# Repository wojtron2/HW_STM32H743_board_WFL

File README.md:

# HW_STM32H743_board_WFL
An STM32H743 KiCad project board

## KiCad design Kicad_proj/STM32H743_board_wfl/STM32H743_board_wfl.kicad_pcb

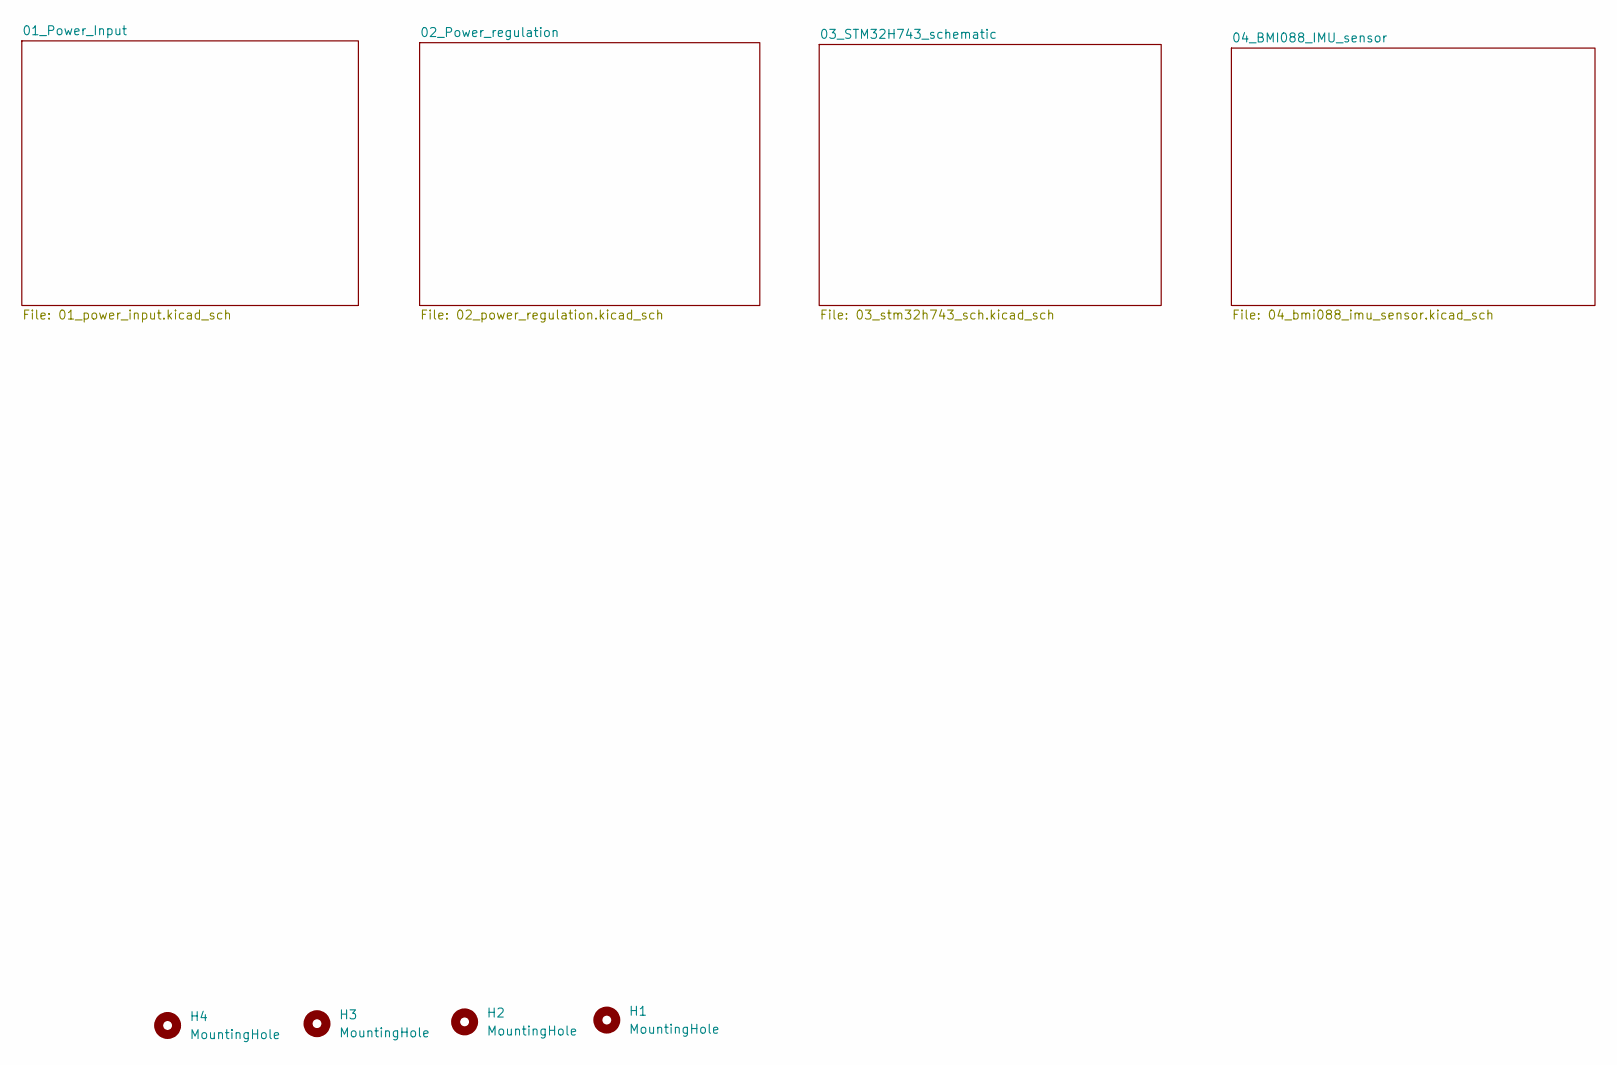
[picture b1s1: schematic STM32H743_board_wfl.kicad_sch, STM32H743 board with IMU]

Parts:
H1, H2, H3, H4: MountingHole; MountingHole_4mm

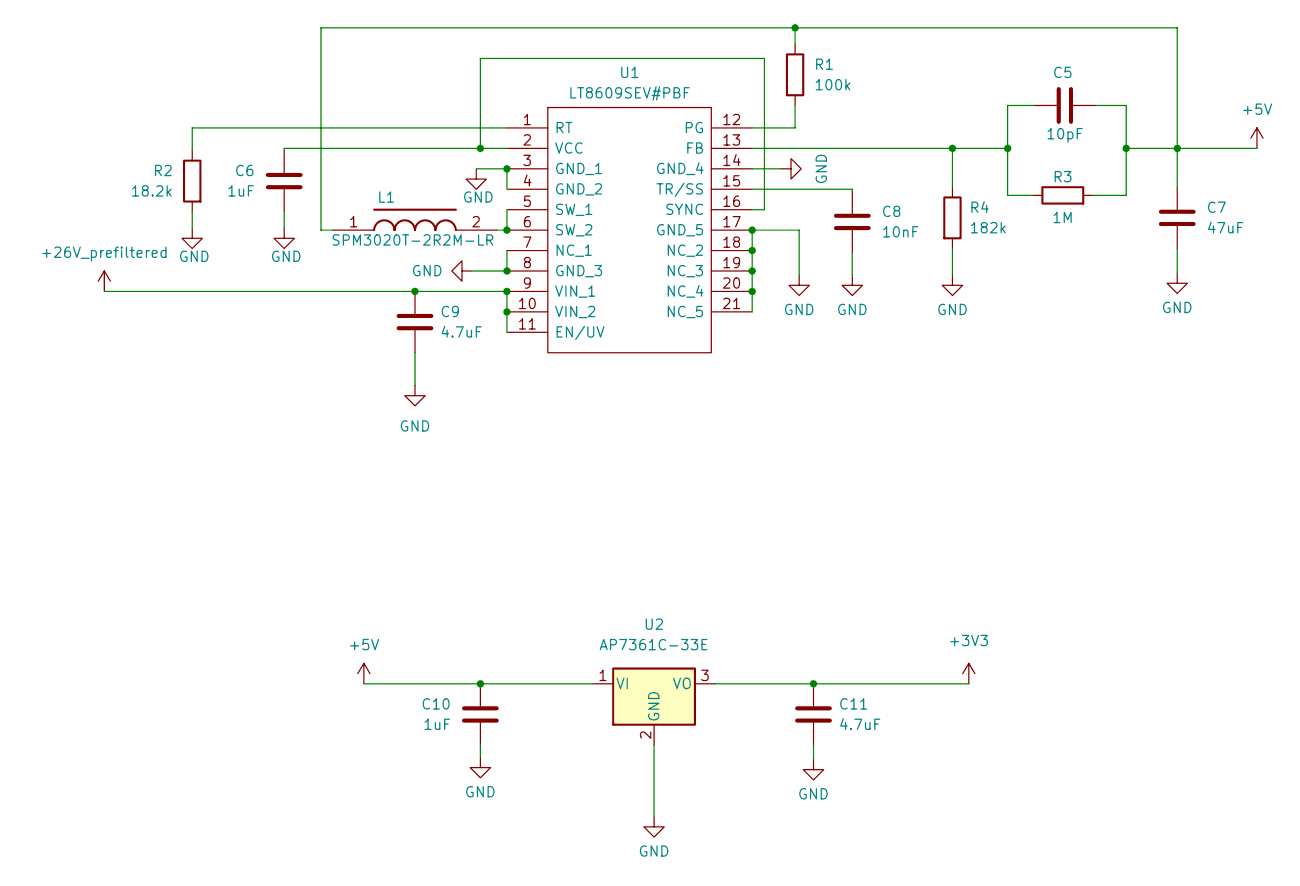
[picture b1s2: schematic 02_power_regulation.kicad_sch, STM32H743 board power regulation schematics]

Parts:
C5: 10pF; C_01005_0402Metric
C6, C10: 1uF; C_0603_1608Metric
C7: 47uF; C_1206_3216Metric
C8: 10nF; C_01005_0402Metric
C9, C11: 4.7uF; C_0603_1608Metric
L1: SPM3020T-2R2M-LR; SPM3010-3020; Mouser Part Number 810-SPM3020T2R2MLR
R1: 100k; R_01005_0402Metric
R2: 18.2k; R_01005_0402Metric
R3: 1M; R_01005_0402Metric
R4: 182k; R_01005_0402Metric
U1: LT8609SEV#PBF; LT8609SEVPBF; Manufacturer_Part_Number LT8609SEV#PBF; Mouser Part Number 584-LT8609SEVPBF
U2: AP7361C-33E; SOT-223-3_TabPin2

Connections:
+5V: C5.2, C7.1, C10.1, L1.1, R1.1, R3.2, U2.1 (VI); also elsewhere on the board
+26V_prefiltered: C9.1, U1.9 (VIN_1), U1.10 (VIN_2), U1.11 (EN/UV); also elsewhere on the board
GND: C6.2, C7.2, C8.2, C9.2, C10.2, C11.2, R2.2, R4.2, U1.3 (GND_1), U1.4 (GND_2), U1.7 (NC_1), U1.8 (GND_3), U1.14 (GND_4), U1.17 (GND_5), U1.18 (NC_2), U1.19 (NC_3), U1.20 (NC_4), U1.21 (NC_5), U2.2 (GND); also elsewhere on the board
unnamed: C5.1, R3.1, R4.1, U1.13 (FB)
unnamed: R1.2, U1.12 (PG)
unnamed: R2.1, U1.1 (RT)
unnamed: L1.2, U1.5 (SW_1), U1.6 (SW_2)
unnamed: C6.1, U1.2 (VCC), U1.16 (SYNC)
unnamed: C8.1, U1.15 (TR/SS)

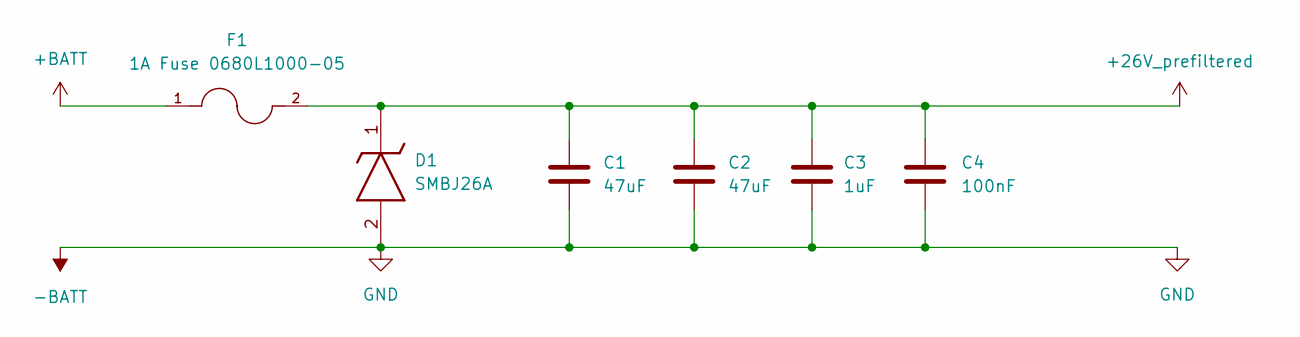
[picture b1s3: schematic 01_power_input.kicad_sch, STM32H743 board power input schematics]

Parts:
C1, C2: 47uF; C_1206_3216Metric
C3: 1uF; C_0603_1608Metric
C4: 100nF; C_01005_0402Metric
D1: SMBJ26A; D_SMB; Manufacturer_Part_Number SMBJ5.0A-E3/5B
F1: 1A Fuse 0680L1000-05; FUSC6125X279N; PARTREV 0679H Apr2019

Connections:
+26V_prefiltered: C1.1, C2.1, C3.1, C4.1, D1.1 (K), F1.2; also elsewhere on the board
+BATT: F1.1; also elsewhere on the board
GND: C1.2, C2.2, C3.2, C4.2, D1.2 (A); also elsewhere on the board

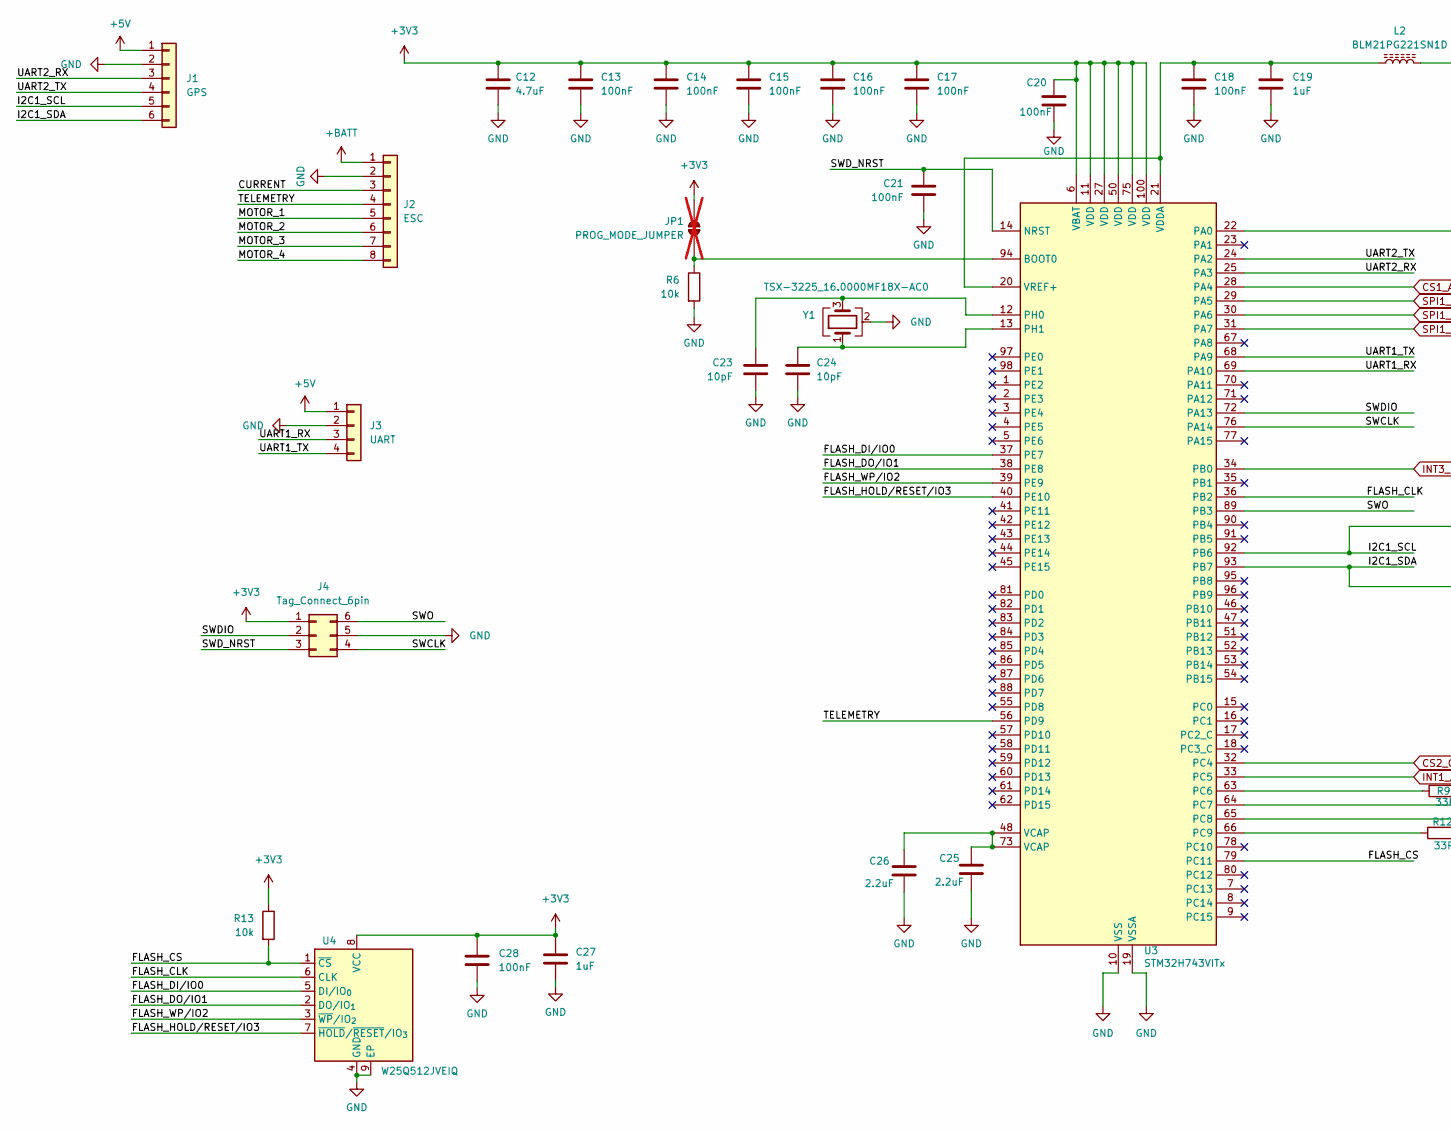
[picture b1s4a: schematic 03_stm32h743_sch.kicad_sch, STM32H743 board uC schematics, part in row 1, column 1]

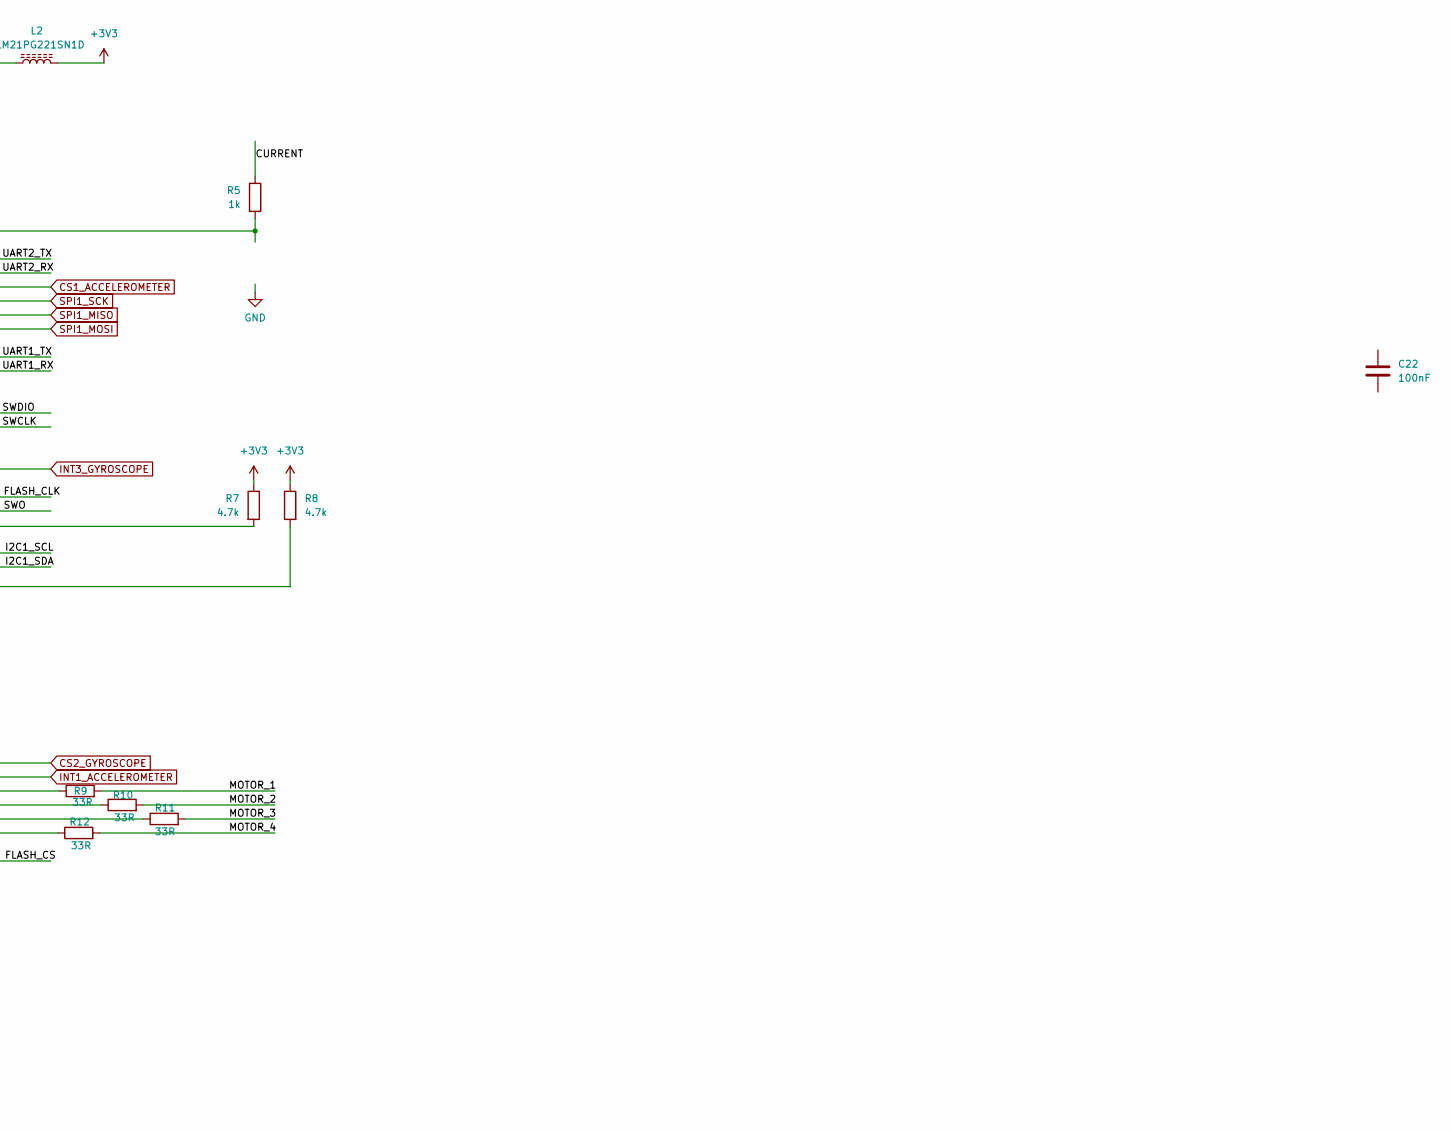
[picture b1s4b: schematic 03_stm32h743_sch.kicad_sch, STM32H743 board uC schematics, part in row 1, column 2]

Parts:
C12: 4.7uF; C_0603_1608Metric
C13, C14, C15, C16, C17, C18, C20, C21, C22, C28: 100nF; C_0402_1005Metric
C19, C27: 1uF; C_0603_1608Metric
C23, C24: 10pF; C_0402_1005Metric
C25, C26: 2.2uF; C_0603_1608Metric
J1: GPS; JST_GH_SM06B-GHS-TB_1x06-1MP_P1.25mm_Horizontal
J2: ESC; JST_GH_SM08B-GHS-TB_1x08-1MP_P1.25mm_Horizontal
J3: UART; JST_GH_SM04B-GHS-TB_1x04-1MP_P1.25mm_Horizontal
J4: Tag_Connect_6pin; Tag-Connect_TC2030-IDC-NL_2x03_P1.27mm_Vertical
JP1: PROG_MODE_JUMPER; R_01005_0402Metric; not fitted
L2: BLM21PG221SN1D; L_0805_2012Metric
R5: 1k; R_01005_0402Metric
R6, R13: 10k; R_01005_0402Metric
R7, R8: 4.7k; R_01005_0402Metric
R9, R10, R11, R12: 33R; R_01005_0402Metric
U3: STM32H743VITx; LQFP-100_14x14mm_P0.5mm
U4: W25Q512JVEIQ; WSON-8-1EP_6x5mm_P1.27mm_EP3.4x4.3mm
Y1: TSX-3225_16.0000MF18X-AC0; Crystal_SMD_3225-4Pin_3.2x2.5mm

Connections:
+5V: J1.1, J3.1; also elsewhere on the board
+BATT: J2.1; also elsewhere on the board
/03_STM32H743_schematic/CURRENT: J2.3, R5.1
/03_STM32H743_schematic/FLASH_CLK: U3.36 (PB2), U4.6 (CLK)
/03_STM32H743_schematic/FLASH_CS: R13.2, U3.79 (PC11), U4.1 (~CS)
/03_STM32H743_schematic/FLASH_DI/IO0: U3.37 (PE7), U4.5 (DI/IO_{0})
/03_STM32H743_schematic/FLASH_DO/IO1: U3.38 (PE8), U4.2 (DO/IO_{1})
/03_STM32H743_schematic/FLASH_HOLD/RESET/IO3: U3.40 (PE10), U4.7 (~HOLD/~RESET/IO_{3})
/03_STM32H743_schematic/FLASH_WP/IO2: U3.39 (PE9), U4.3 (~WP/IO_{2})
/03_STM32H743_schematic/I2C1_SCL: J1.5, R7.2, U3.92 (PB6)
/03_STM32H743_schematic/I2C1_SDA: J1.6, R8.2, U3.93 (PB7)
/03_STM32H743_schematic/MOTOR_1: J2.5, R9.2
/03_STM32H743_schematic/MOTOR_2: J2.6, R10.2
/03_STM32H743_schematic/MOTOR_3: J2.7, R11.2
/03_STM32H743_schematic/MOTOR_4: J2.8, R12.2
/03_STM32H743_schematic/SWCLK: J4.4, U3.76 (PA14)
/03_STM32H743_schematic/SWDIO: J4.2, U3.72 (PA13)
/03_STM32H743_schematic/SWD_NRST: C21.1, J4.3, U3.14 (NRST)
/03_STM32H743_schematic/SWO: J4.6, U3.89 (PB3)
/03_STM32H743_schematic/TELEMETRY: J2.4, U3.56 (PD9)
/03_STM32H743_schematic/UART1_RX: J3.3, U3.69 (PA10)
/03_STM32H743_schematic/UART1_TX: J3.4, U3.68 (PA9)
/03_STM32H743_schematic/UART2_RX: J1.3, U3.25 (PA3)
/03_STM32H743_schematic/UART2_TX: J1.4, U3.24 (PA2)
CS1_ACCELEROMETER: U3.28 (PA4); also elsewhere on the board
CS2_GYROSCOPE: U3.32 (PC4); also elsewhere on the board
GND: C12.2, C13.2, C14.2, C15.2, C16.2, C17.2, C18.2, C19.2, C20.2, C21.2, C22.2, C23.2, C24.2, C25.2, C26.2, C27.2, C28.2, J1.2, J2.2, J3.2, J4.5, R6.2, U3.10 (VSS), U3.19 (VSSA), U3.26 (VSS), U3.49 (VSS), U3.74 (VSS), U3.99 (VSS), U4.4 (GND), U4.9 (EP), Y1.2 (G), Y1.4 (G); also elsewhere on the board
INT1_ACCELEROMETER: U3.33 (PC5); also elsewhere on the board
INT3_GYROSCOPE: U3.34 (PB0); also elsewhere on the board
unnamed: C25.1, C26.1, U3.48 (VCAP), U3.73 (VCAP)
unnamed: JP1.1 (A), R6.1, U3.94 (BOOT0)
unnamed: R9.1, U3.63 (PC6)
unnamed: R10.1, U3.64 (PC7)
unnamed: R11.1, U3.65 (PC8)
unnamed: R12.1, U3.66 (PC9)
unnamed: C23.1, U3.12 (PH0), Y1.3
unnamed: C24.1, U3.13 (PH1), Y1.1
unnamed: C18.1, C19.1, L2.1, U3.20 (VREF+), U3.21 (VDDA)
SPI1_MISO: U3.30 (PA6); also elsewhere on the board
SPI1_MOSI: U3.31 (PA7); also elsewhere on the board
SPI1_SCK: U3.29 (PA5); also elsewhere on the board

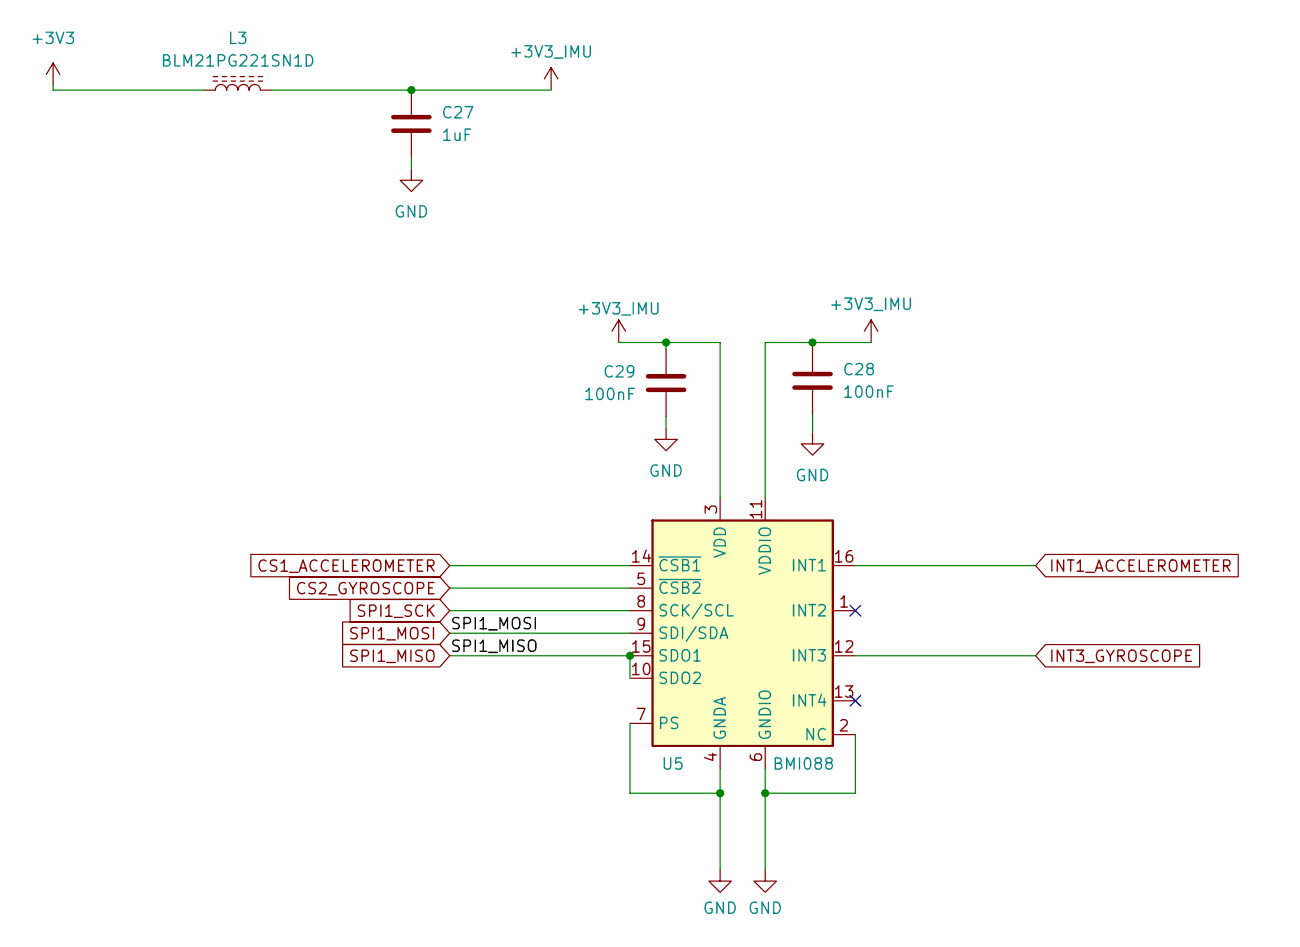
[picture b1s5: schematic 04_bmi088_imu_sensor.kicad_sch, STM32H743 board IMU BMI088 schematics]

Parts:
C27: 1uF; C_0603_1608Metric
C28, C29: 100nF; C_0402_1005Metric
L3: BLM21PG221SN1D; L_0805_2012Metric
U5: BMI088; Bosch_LGA-16_4.5x3mm_P0.5mm_LayoutBorder7x1y_ClockwisePinNu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

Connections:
CS1_ACCELEROMETER: U5.14 (~CSB1); also elsewhere on the board
CS2_GYROSCOPE: U5.5 (~CSB2); also elsewhere on the board
GND: C27.2, C28.2, C29.2, U5.2 (GNDA), U5.4 (GNDA), U5.6 (GNDIO), U5.7 (PS); also elsewhere on the board
INT1_ACCELEROMETER: U5.16 (INT1); also elsewhere on the board
INT3_GYROSCOPE: U5.12 (INT3); also elsewhere on the board
SPI1_MISO: U5.10 (SDO2), U5.15 (SDO1); also elsewhere on the board
SPI1_MOSI: U5.9 (SDI/SDA); also elsewhere on the board
SPI1_SCK: U5.8 (SCK/SCL); also elsewhere on the board

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
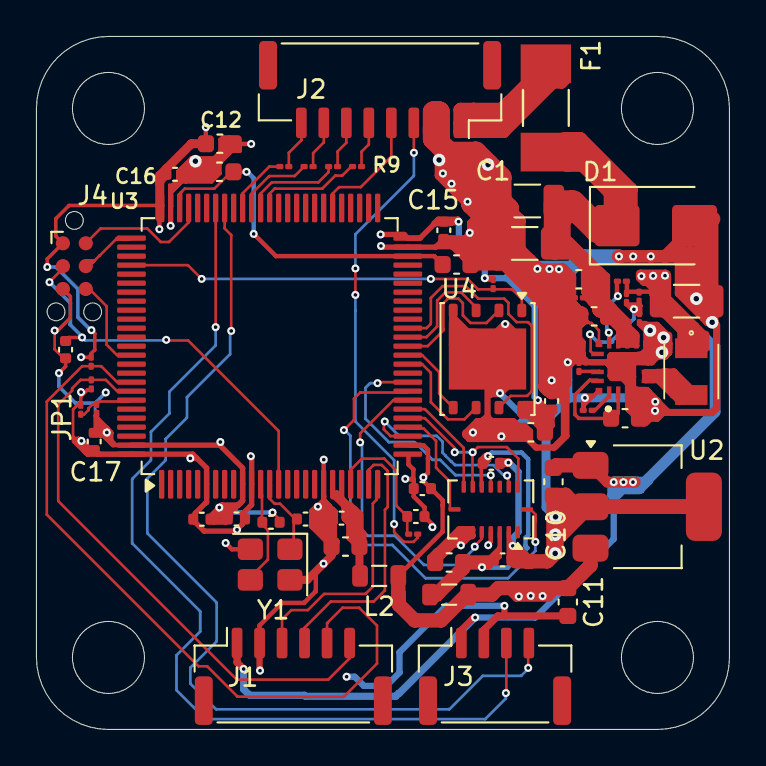
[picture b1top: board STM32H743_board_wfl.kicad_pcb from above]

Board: 4 copper layers, 38.5 x 38.5 mm, 64 parts (0 on the bottom side), 51 nets.

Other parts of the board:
C30, C31: 100nF; C_0402_1005Metric

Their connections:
GND: C30.2, C31.2; also elsewhere on the board

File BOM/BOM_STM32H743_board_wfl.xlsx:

Oznaczenie | Footprint | Liczba | Oznaczenie | Dostawca i numer artykuĹ‚u
C1, C2, C7 | C_1206_3216Metric | 3 | 47uF
C3, C6, C10, C19, C27, C29 | C_0603_1608Metric | 6 | 1uF
C4 | C_01005_0402Metric | 1 | 100nF
C5 | C_01005_0402Metric | 1 | 10pF
C8 | C_01005_0402Metric | 1 | 10nF
C9, C11, C12 | C_0603_1608Metric | 3 | 4.7uF
C13, C14, C15, C16, C17, C18, C20, C21, C22, C28, C30, C31 | C_0402_1005Metric | 12 | 100nF
C23, C24 | C_0402_1005Metric | 2 | 10pF
C25, C26 | C_0603_1608Metric | 2 | 2.2uF
D1 | D_SMB | 1 | SMBJ26A
F1 | FUSC6125X279N | 1 | 1A Fuse 0680L1000-05
J1 | JST_GH_SM06B-GHS-TB_1x06-1MP_P1.25mm_Horizontal | 1 | GPS
J2 | JST_GH_SM08B-GHS-TB_1x08-1MP_P1.25mm_Horizontal | 1 | ESC
J3 | JST_GH_SM04B-GHS-TB_1x04-1MP_P1.25mm_Horizontal | 1 | UART
J4 | Tag-Connect_TC2030-IDC-NL_2x03_P1.27mm_Vertical | 1 | Tag_Connect_6pin
L1 | SPM3010-3020 | 1 | SPM3020T-2R2M-LR
L2, L3 | L_0805_2012Metric | 2 | BLM21PG221SN1D
R1 | R_01005_0402Metric | 1 | 100k
R2 | R_01005_0402Metric | 1 | 18.2k
R3 | R_01005_0402Metric | 1 | 1M
R4 | R_01005_0402Metric | 1 | 182k
R5 | R_01005_0402Metric | 1 | 1k
R6, R13 | R_01005_0402Metric | 2 | 10k
R7, R8 | R_01005_0402Metric | 2 | 4.7k
R9, R10, R11, R12 | R_01005_0402Metric | 4 | 33R
U1 | LT8609SEVPBF | 1 | LT8609SEV#PBF
U2 | SOT-223-3_TabPin2 | 1 | AP7361C-33E
U3 | LQFP-100_14x14mm_P0.5mm | 1 | STM32H743VITx
U4 | WSON-8-1EP_6x5mm_P1.27mm_EP3.4x4.3mm | 1 | W25Q512JVEIQ
U5 | Bosch_LGA-16_4.5x3mm_P0.5mm_LayoutBorder7x1y_ClockwisePinNumbering | 1 | BMI088
Y1 | Crystal_SMD_3225-4Pin_3.2x2.5mm | 1 | TSX-3225_16.0000MF18X-AC0
